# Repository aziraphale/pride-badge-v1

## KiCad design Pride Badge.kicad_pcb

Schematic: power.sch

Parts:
C1: 10nF; C_0805
C2: 100nF; C_0805
C3: 4.7µF; C_0805
C4, C5: 22µF; C_0805
C6, C7: 33µF; C_0805
C8: 100n; C_0805
C18: 10µF; C_0805
D1: SS34; D_SMA
D2: LED_GREEN1_RED2; LED_0606 (Dual - 0603x2)
F1: 500mA/8V; Fuse_SMD1206_Reflow
J1: USB_B_Micro; USB_Micro-B_OSHPark
J2: Conn_01x02; JST_PH_S2B-PH-SM4-TB_02x2.00mm_Angled
L1: L; inductor_smd_0805
L2: 22µH; Inductor_Wurth_HCM-7070
R1: 100k; R_0805
R2, R5, R6, R8: 1k; R_0805
R3: 1k2; R_0805
R4: 7.5k; R_0805
R7: 100R; R_0805
R22: 2k7; R_0805
SW1: SW_DPDT_x2; Switch_Slide_JS202011SCQN
SW7: SW_DPDT_x2; SW_SPDT_PCM12
TP1: TP_USBDM; Test_Point_1mm
TP2: TP_VUSB; Test_Point_1mm
TP3: TP_5V; Test_Point_1mm
TP4: TP_3V3; Test_Point_1mm
TP5: TP_GND; Test_Point_1mm
TP6: TP_BATT+; Test_Point_1mm
TP7: TP_BATT-; Test_Point_1mm
TP8: TP_USBDP; Test_Point_1mm
TP9: TP_CHRGVCC; Test_Point_1mm
U1: USBLC6-2SC6; SOT23-6L
U2: TP4056; SOIC-8-1EP_W3.9mm
U3: MT3608; SOT-23-6
U4: AZ1117EH-3.3; SOT-223; MPN NCP1117ST33T3G; Digi-Key_PN NCP1117ST33T3GOSCT-ND
U5: FS312F; SOT-23-6
U6: FS8205; SOT-23-6

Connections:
+3V3: C7.1, TP4.1, U4.2 (OUT), U4.4 (OUT/TAB); also elsewhere on the board
+5V: C5.1, C6.1, D1.1, R4.1, TP3.1, U4.3 (IN); also elsewhere on the board
+BATT: C18.1, J2.2, R7.1, SW1.1, SW1.4, TP6.1, U2.5; also elsewhere on the board
-BATT: C8.2, J2.1, TP7.1, U5.6, U6.1
/SheetPower/VUSB: C1.1, J1.1, L1.1, TP2.1, U1.5
GND: C1.2, C2.2, C3.2, C4.2, C5.2, C6.2, C7.2, C18.2, J1.5, J1.6, R1.2, R3.1, R6.2, R8.2, R22.1, TP5.1, U1.2, U2.1, U2.3, U2.9, U3.2, U4.1 (ADJ/GND), U6.3; also elsewhere on the board
unnamed: C2.1, C3.1, D2.1, D2.2, L1.2, TP9.1, U2.4, U2.8
unnamed: C4.1, F1.1, L2.1, U3.4, U3.5
unnamed: C8.1, R7.2, U5.5
unnamed: D1.2, L2.2, U3.1
unnamed: D2.3, R5.2
unnamed: D2.4, R2.2
unnamed: F1.2, SW1.2, SW1.5
unnamed: J1.2, U1.1
unnamed: J1.3, U1.3
unnamed: J1.4, R1.1
unnamed: R2.1, U2.7
unnamed: R3.2, SW7.1
unnamed: R4.2, R6.1, U3.3
unnamed: R5.1, U2.6
unnamed: R8.1, U5.2
unnamed: R22.2, SW7.3
unnamed: SW7.2, U2.2
unnamed: U5.1, U6.6
unnamed: U5.3, U6.4
unnamed: U6.2, U6.5
USBDM: TP1.1, U1.6; also elsewhere on the board
USBDP: TP8.1, U1.4; also elsewhere on the board

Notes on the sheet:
Vout = Vref * (1 + (R1/R2) ) Where Vref = 0.6V, thus Vout = 0.6 * (1 + (7500 / 1000) ) = 5.1V
Charge current selection. 1k2 = 1A 2k7 = 444mA

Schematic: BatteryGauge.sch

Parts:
C16: 10µF; C_0805
C17: 100n; C_0805
D3: 2V5 Zener; D_MiniMELF_Handsoldering
D4: LED_BLUE; D_0805
D5: LED_GREEN; D_0805
D6: LED_YELLOW; D_0805
D7: LED_ORANGE; D_0805
D8: LED_RED; D_0805
R13, R19: 1k; R_0805
R14, R16, R20: 680R; R_0805
R15, R24: 2k; R_0805
R17: 4k3; R_0805
R18: 1M; R_0805
R21: 1k2; R_0805
R23: 8k66; R_0805
R25: 27k; R_0805
R26: 30k; R_0805
R27: 3k3; R_0805
SW6: SW_SeeBattGauge; Btn_SMD_6x3.5mm
TP10: TP_339+_BLUE; Test_Point_1mm
TP11: TP_339+_GREEN; Test_Point_1mm
TP12: TP_339+_YELLOW; Test_Point_1mm
TP13: TP_555THRES; Test_Point_1mm
TP14: TP_555OUT; Test_Point_1mm
TP15: TP_339+_ORANGE; Test_Point_1mm
TP16: TP_339-; Test_Point_1mm
TP27: TP_GND; Test_Point_1mm
TP30: TP_555TRIG; Test_Point_1mm
U9: LM339; SOIC-14_W3.9mm
U10: 555; SOIC-8_W3.9mm

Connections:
+5V: R18.1, R19.1, U9.3 (V+), U10.4, U10.8; also elsewhere on the board
+BATT: R13.1, R25.1; also elsewhere on the board
/SheetBatteryGauge/LED_VCC: R15.1, R17.1, R21.1, R24.1, R27.1, TP14.1, U10.3
GND: C16.2, C17.2, D3.2, D8.1, R23.2, R26.2, SW6.1, TP27.1, U9.12 (V-), U10.1; also elsewhere on the board
unnamed: C16.1, R18.2, TP13.1, U10.6, U10.7
unnamed: C17.1, U10.5
unnamed: D3.1, R13.2, R14.1, TP10.1, U9.5 (+)
unnamed: D4.1, U9.2
unnamed: D4.2, R15.2
unnamed: D5.1, U9.1
unnamed: D5.2, R17.2
unnamed: D6.1, U9.13
unnamed: D6.2, R21.2
unnamed: D7.1, U9.14
unnamed: D7.2, R24.2
unnamed: D8.2, R27.2
unnamed: R14.2, R16.1, TP11.1, U9.7 (+)
unnamed: R16.2, R20.1, TP12.1, U9.11 (+)
unnamed: R19.2, SW6.2, TP30.1, U10.2
unnamed: R20.2, R23.1, TP15.1, U9.9 (+)
unnamed: R25.2, R26.1, TP16.1, U9.4 (-), U9.6 (-), U9.8 (-), U9.10 (-)

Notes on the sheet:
~~1.95V here

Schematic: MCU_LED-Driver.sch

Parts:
C9, C13, C15: 100nF; C_0805
C10: 4.7µF; C_0805
C11: 10nF; C_0805
C12, C14: 1µF; C_0805
D9: LED_Small; LED_0805
DA1: LED_1x1; D_0805
DA2: LED_1x2; D_0805
DA3: LED_1x3; D_0805
DB1: LED_2x1; D_0805
DB2: LED_2x2; D_0805
DB3: LED_2x3; D_0805
DC1: LED_3x1; D_0805
DC2: LED_3x2; D_0805
DC3: LED_3x3; D_0805
DD1: LED_4x1; D_0805
DD2: LED_4x2; D_0805
DD3: LED_4x3; D_0805
DE1: LED_5x1; D_0805
DE2: LED_5x2; D_0805
DE3: LED_5x3; D_0805
DF1: LED_6x1; D_0805
DF2: LED_6x2; D_0805
DF3: LED_6x3; D_0805
J3: Custom_SWD; bb02-hy05a
R9, R10: 4k7; R_0805
R11: 100k; R_0805
R12: 3k9; R_0805
R28: 2k7; R_0805
R29: 10k; R_0805
SW2: Mode_BTN; Btn_SMD_6x3.5mm
SW3: Bright_BTN; Btn_SMD_6x3.5mm
SW4: Reset_BTN; Tiny_SMD_Side_Btn_4x2.5mm
SW5: Boot_BTN; Tiny_SMD_Side_Btn_4x2.5mm
TP17: TP_MODEBTN; Test_Point_1mm
TP18: TP_BRIGHTBTN; Test_Point_1mm
TP19: TP_SWDIO; Test_Point_1mm
TP20: TP_SWCLK; Test_Point_1mm
TP21, TP25: TP_~RST; Test_Point_1mm
TP22: TP_SDA; Test_Point_1mm
TP23: TP_SCL; Test_Point_1mm
TP24: TP_IS_SDB; Test_Point_1mm
TP26: TP_BOOT; Test_Point_1mm
TP28: TP_GND; Test_Point_1mm
TP29: TP_3V3; Test_Point_1mm
U7: STM32F042F6P6; TSSOP-20_W4.4mm
U8: IS31FL3218; SOIC-24_W7.50mm

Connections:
+3V3: C9.1, C10.1, C11.1, C12.1, J3.1, SW5.1, TP29.1, U7.5, U7.16; also elsewhere on the board
+5V: C14.1, C15.1, DA1.2, DA2.2, DA3.2, DB1.2, DB2.2, DB3.2, DC1.2, DC2.2, DC3.2, DD1.2, DD2.2, DD3.2, DE1.2, DE2.2, DE3.2, DF1.2, DF2.2, DF3.2, R9.1, R10.1, U8.3; also elsewhere on the board
/Sheet_MCU-LED-Driver/ISSI_SDB: R11.1, TP24.1, U7.9, U8.24
/Sheet_MCU-LED-Driver/RESET: C13.1, J3.4, SW4.2, TP21.1, TP25.1, U7.4
/Sheet_MCU-LED-Driver/SCL0: R10.2, TP23.1, U7.3, U8.6
/Sheet_MCU-LED-Driver/SDA0: R9.2, TP22.1, U7.2, U8.5
/Sheet_MCU-LED-Driver/SWCLK: J3.3, TP20.1, U7.20
/Sheet_MCU-LED-Driver/SWDIO: J3.2, TP19.1, U7.19
GND: C9.2, C10.2, C11.2, C12.2, C13.2, C14.2, C15.2, D9.1, J3.5, R11.2, R12.2, R29.2, SW2.2, SW3.2, SW4.1, TP28.1, U7.15, U8.4; also elsewhere on the board
unnamed: D9.2, R28.1
unnamed: DA1.1, U8.7
unnamed: DA2.1, U8.8
unnamed: DA3.1, U8.9
unnamed: DB1.1, U8.10
unnamed: DB2.1, U8.11
unnamed: DB3.1, U8.12
unnamed: DC1.1, U8.13
unnamed: DC2.1, U8.14
unnamed: DC3.1, U8.15
unnamed: DD1.1, U8.16
unnamed: DD2.1, U8.17
unnamed: DD3.1, U8.18
unnamed: DE1.1, U8.19
unnamed: DE2.1, U8.20
unnamed: DE3.1, U8.21
unnamed: DF1.1, U8.22
unnamed: DF2.1, U8.23
unnamed: DF3.1, U8.1
unnamed: R12.1, U8.2
unnamed: R28.2, U7.11
unnamed: R29.1, SW5.2, TP26.1, U7.1
unnamed: SW2.1, TP17.1, U7.6
unnamed: SW3.1, TP18.1, U7.7
USBDM: U7.17; also elsewhere on the board
USBDP: U7.18; also elsewhere on the board

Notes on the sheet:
Max LED current is: I_max = 58.5 * (1.3 / R_ext) R_ext = 3k3 => 23mA R_ext = 3k6 => 21mA R_ext = 3k9 => 19.5mA
GND to boot normally; 3V3 to boot to bootloader

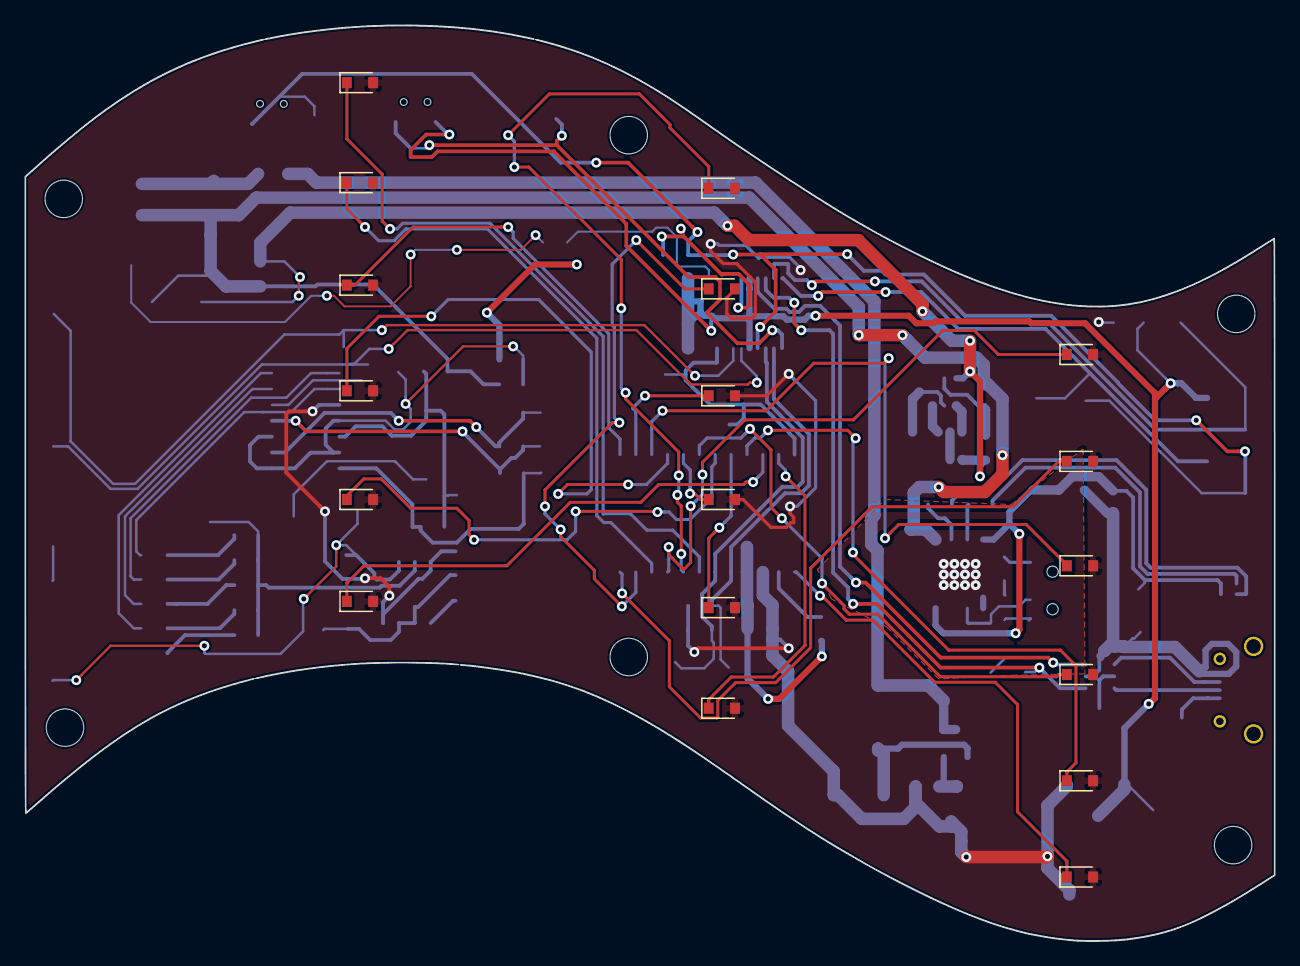
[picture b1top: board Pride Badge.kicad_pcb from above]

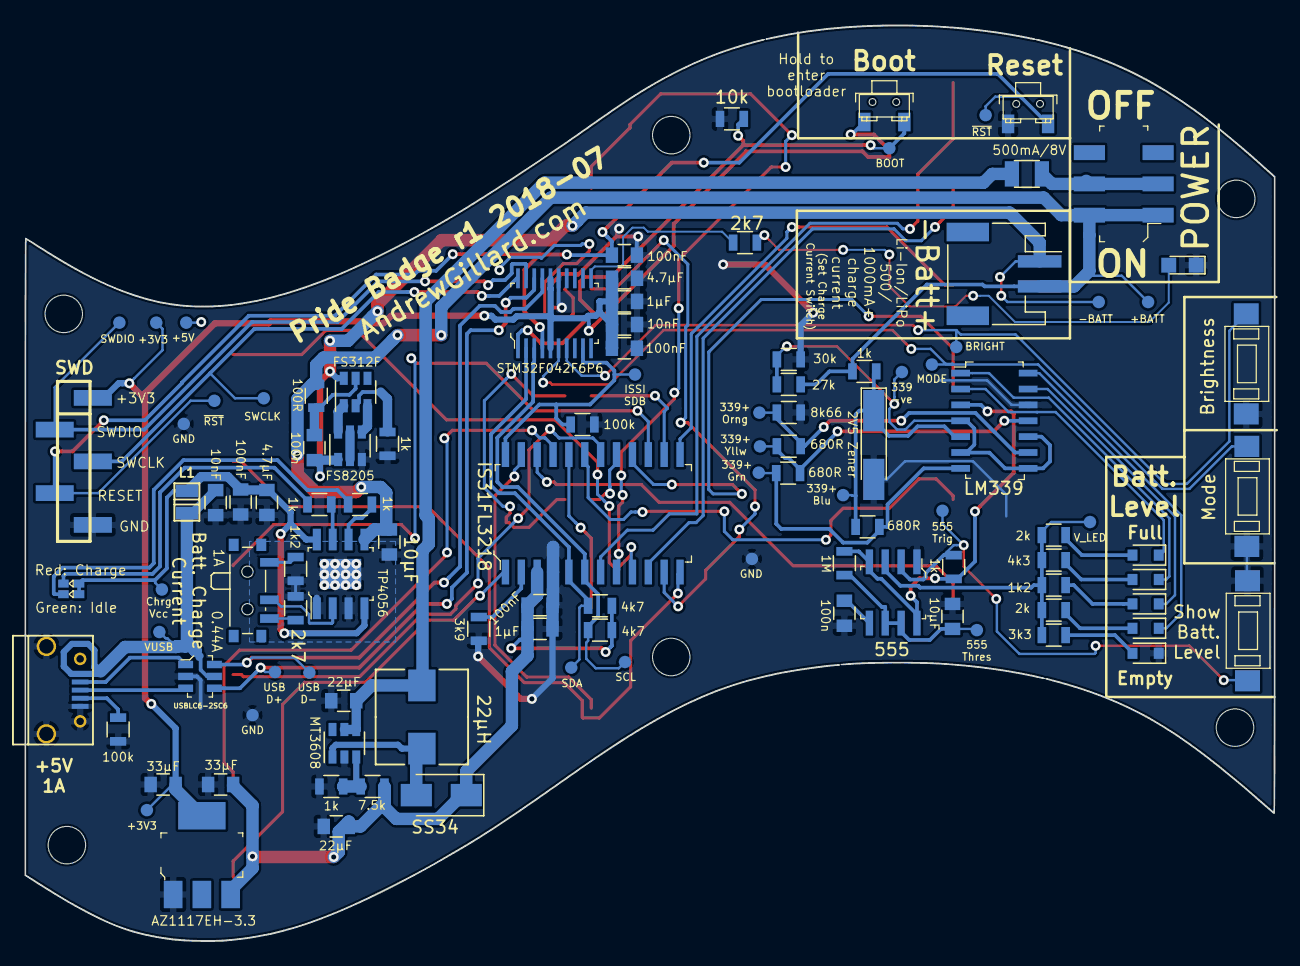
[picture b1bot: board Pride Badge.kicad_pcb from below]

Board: 2 copper layers, 100.0 x 73.3 mm, 129 parts (109 on the bottom side), 76 nets.

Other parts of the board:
Outline_Eco2: pride_badge_outline_100x73
board_edge_cuts: pride_badge_edge-cuts

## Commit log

2018-06-27 Add gitignore
2018-06-27 Add notes and calculations so far
2018-06-27 Add empty KiCad project
2018-06-28 Schematics almost finished (Chinese parts)
    Just need passives, etc., around MCU. Maybe then swap out Chinese parts with RoHS-compliant ones...
2018-06-30 Schematics complete, ready for prototype PCBs to be designed
2018-06-30 Fix footprint of dual 0603 LED
2018-06-30 Prototype PCB laid out, no tracks yet
2018-06-30 Prototype PCB design finished?
2018-07-01 Prototype PCB gerbers plotted & PCB layout tweaked
2018-07-01 Fixed footprints for a few ICs. Oops.
    Updated PCB layout to come!
2018-07-01 Fixed up PCB design after fixing some IC footprints
2018-07-07 More fixes after testing the LED gauge and such
2018-07-07 More fixes after prototyping & reading more datasheets
2018-07-07 Hopefully final schematic fixes
2018-07-13 Imported flag shape into outline layer & finished layout
2018-07-13 Ordered rev1 gerbers
2018-07-15 PDF versions of gerbers
2018-07-15 Initial firmware version
2018-07-15 Oops, turn all the LEDs *off* rather than *on* :)
